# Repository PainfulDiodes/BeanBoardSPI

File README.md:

# BeanBoardSPI

_SPI controller in 74' logic for [BeanBoard](https://github.com/PainfulDiodes/BeanBoard) / [BeanZee](https://github.com/PainfulDiodes/BeanZee) Z80 computer._

SPI is a fast serial interface commonly used for connecting microcontrollers to peripherals like SD cards, displays and sensors.

The intent of this design is to provide access to an [RA8875](https://www.adafruit.com/product/1590) TFT panel controller and to [flash memory modules](https://www.adafruit.com/product/5635) on my Z80 homebrew computer. The [Marvin](https://github.com/PainfulDiodes/marvin) monitor program provides software support for this configuration.

For background, please see the [accompanying blog posts](https://painfuldiodes.wordpress.com/category/beanboardspi/).

*Thank you to those helpful folks at [PCBWay](https://pcbway.com) who sponsored this build and provided the PCBs*

&nbsp;

BeanBoardSPI Rev B populated with Adafruit SPI modules

SPI timing

BeanBoardSPI Rev A Plugged into BeanBoard with BeanZee, and a TFT panel

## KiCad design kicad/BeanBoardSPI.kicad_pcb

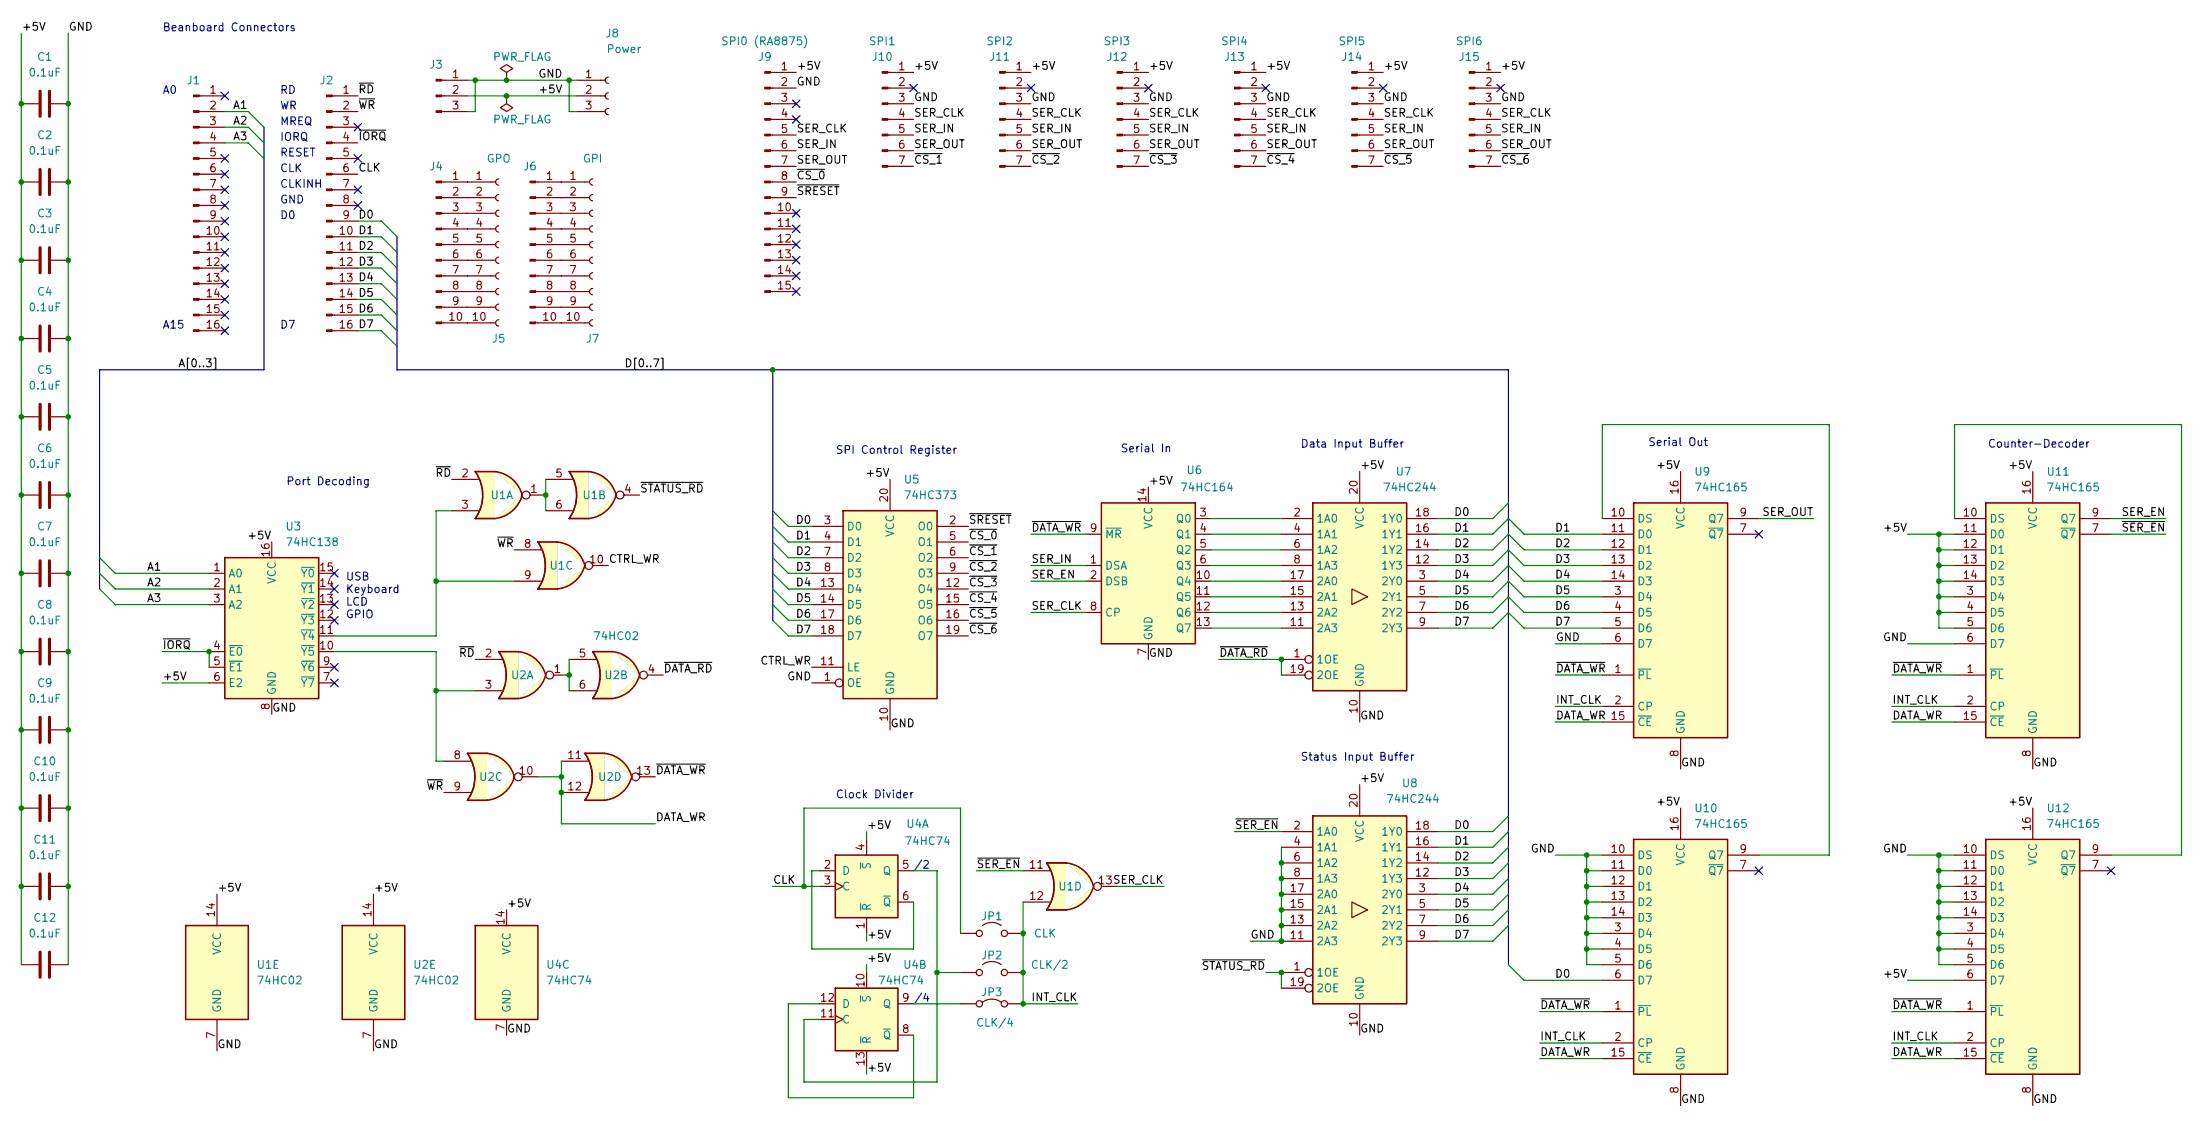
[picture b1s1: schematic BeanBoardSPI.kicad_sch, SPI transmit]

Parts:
C1, C2, C3, C4, C5, C6, C7, C8, C9, C10, C11, C12: 0.1uF; C_Disc_D5.0mm_W2.5mm_P2.50mm
J1, J2: Conn_01x16_Pin; PinHeader_1x16_P2.54mm_Vertical
J3: Conn_01x03_Pin; PinHeader_1x03_P2.54mm_Vertical
J4, J6: Conn_01x10_Pin; PinHeader_1x10_P2.54mm_Vertical
J5: GPO; PinSocket_1x10_P2.54mm_Vertical
J7: GPI; PinSocket_1x10_P2.54mm_Vertical
J8: Power; PinSocket_1x03_P2.54mm_Vertical
J9: SPI0 (RA8875); PinHeader_1x15_P2.54mm_Vertical
J10: SPI1; PinHeader_1x07_P2.54mm_Vertical
J11: SPI2; PinHeader_1x07_P2.54mm_Vertical
J12: SPI3; PinHeader_1x07_P2.54mm_Vertical
J13: SPI4; PinHeader_1x07_P2.54mm_Vertical
J14: SPI5; PinHeader_1x07_P2.54mm_Vertical
J15: SPI6; PinHeader_1x07_P2.54mm_Vertical
JP1: CLK; PinHeader_1x02_P2.54mm_Vertical
JP2: CLK/2; PinHeader_1x02_P2.54mm_Vertical
JP3: CLK/4; PinHeader_1x02_P2.54mm_Vertical
U1, U2: 74HC02; DIP-14_W7.62mm_Socket
U3: 74HC138; DIP-16_W7.62mm_Socket
U4: 74HC74; DIP-14_W7.62mm_Socket
U5: 74HC373; DIP-20_W7.62mm_Socket
U6: 74HC164; DIP-14_W7.62mm_Socket
U7, U8: 74HC244; DIP-20_W7.62mm_Socket
U9, U10, U11, U12: 74HC165; DIP-16_W7.62mm_Socket

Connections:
/+5V: C1.1, C2.1, C3.1, C4.1, C5.1, C6.1, C7.1, C8.1, C9.1, C10.1, C11.1, C12.1, J3.2, J8.2, J9.1, J10.1, J11.1, J12.1, J13.1, J14.1, J15.1, U1.14 (VCC), U2.14 (VCC), U3.6 (E2), U3.16 (VCC), U4.1 (~R), U4.4 (~S), U4.10 (~S), U4.13 (~R), U4.14 (VCC), U5.20 (VCC), U6.14 (VCC), U7.20 (VCC), U8.20 (VCC), U9.16 (VCC), U10.16 (VCC), U11.3 (D4), U11.4 (D5), U11.5 (D6), U11.11 (D0), U11.12 (D1), U11.13 (D2), U11.14 (D3), U11.16 (VCC), U12.6 (D7), U12.16 (VCC)
/A1: J1.2, U3.1 (A0)
/A2: J1.3, U3.2 (A1)
/A3: J1.4, U3.3 (A2)
/CLK: J2.6, JP1.1 (A), U4.3 (C)
/CTRL_WR: U1.10, U5.11 (LE)
/D0: J2.9, U5.3 (D0), U7.18 (1Y0), U8.18 (1Y0), U10.6 (D7)
/D1: J2.10, U5.4 (D1), U7.16 (1Y1), U8.16 (1Y1), U9.11 (D0)
/D2: J2.11, U5.7 (D2), U7.14 (1Y2), U8.14 (1Y2), U9.12 (D1)
/D3: J2.12, U5.8 (D3), U7.12 (1Y3), U8.12 (1Y3), U9.13 (D2)
/D4: J2.13, U5.13 (D4), U7.3 (2Y0), U8.3 (2Y0), U9.14 (D3)
/D5: J2.14, U5.14 (D5), U7.5 (2Y1), U8.5 (2Y1), U9.3 (D4)
/D6: J2.15, U5.17 (D6), U7.7 (2Y2), U8.7 (2Y2), U9.4 (D5)
/D7: J2.16, U5.18 (D7), U7.9 (2Y3), U8.9 (2Y3), U9.5 (D6)
/DATA_WR: U2.10, U2.11, U2.12, U9.15 (~CE), U10.15 (~CE), U11.15 (~CE), U12.15 (~CE)
/GND: C1.2, C2.2, C3.2, C4.2, C5.2, C6.2, C7.2, C8.2, C9.2, C10.2, C11.2, C12.2, J3.1, J3.3, J8.1, J8.3, J9.2, J10.3, J11.3, J12.3, J13.3, J14.3, J15.3, U1.7 (GND), U2.7 (GND), U3.8 (GND), U4.7 (GND), U5.1 (OE), U5.10 (GND), U6.7 (GND), U7.10 (GND), U8.4 (1A1), U8.6 (1A2), U8.8 (1A3), U8.10 (GND), U8.11 (2A3), U8.13 (2A2), U8.15 (2A1), U8.17 (2A0), U9.6 (D7), U9.8 (GND), U10.3 (D4), U10.4 (D5), U10.5 (D6), U10.8 (GND), U10.10 (DS), U10.11 (D0), U10.12 (D1), U10.13 (D2), U10.14 (D3), U11.6 (D7), U11.8 (GND), U12.3 (D4), U12.4 (D5), U12.5 (D6), U12.8 (GND), U12.10 (DS), U12.11 (D0), U12.12 (D1), U12.13 (D2), U12.14 (D3)
/INT_CLK: JP1.2 (B), JP2.2 (B), JP3.2 (B), U1.12, U9.2 (CP), U10.2 (CP), U11.2 (CP), U12.2 (CP)
/SER_CLK: J9.5, J10.4, J11.4, J12.4, J13.4, J14.4, J15.4, U1.13, U6.8 (CP)
/SER_EN: U6.2 (DSB), U11.9 (Q7)
/SER_IN: J9.6, J10.5, J11.5, J12.5, J13.5, J14.5, J15.5, U6.1 (DSA)
/SER_OUT: J9.7, J10.6, J11.6, J12.6, J13.6, J14.6, J15.6, U9.9 (Q7)
/~CS_0: J9.8, U5.5 (O1)
/~CS_1: J10.7, U5.6 (O2)
/~CS_2: J11.7, U5.9 (O3)
/~CS_3: J12.7, U5.12 (O4)
/~CS_4: J13.7, U5.15 (O5)
/~CS_5: J14.7, U5.16 (O6)
/~CS_6: J15.7, U5.19 (O7)
/~DATA_RD: U2.4, U7.1 (1OE), U7.19 (2OE)
/~DATA_WR: U2.13, U6.9 (~MR), U9.1 (~PL), U10.1 (~PL), U11.1 (~PL), U12.1 (~PL)
/~IORQ: J2.4, U3.4 (~E0), U3.5 (~E1)
/~RD: J2.1, U1.2, U2.2
/~SER_EN: U1.11, U8.2 (1A0), U11.7 (~Q7)
/~SRESET: J9.9, U5.2 (O0)
/~STATUS_RD: U1.4, U8.1 (1OE), U8.19 (2OE)
/~WR: J2.2, U1.8, U2.9
unnamed: J4.1, J5.1
unnamed: J4.2, J5.2
unnamed: J4.3, J5.3
unnamed: J4.4, J5.4
unnamed: J4.5, J5.5
unnamed: J4.6, J5.6
unnamed: J4.7, J5.7
unnamed: J4.8, J5.8
unnamed: J4.9, J5.9
unnamed: J4.10, J5.10
unnamed: J6.1, J7.1
unnamed: J6.2, J7.2
unnamed: J6.3, J7.3
unnamed: J6.4, J7.4
unnamed: J6.5, J7.5
unnamed: J6.6, J7.6
unnamed: J6.7, J7.7
unnamed: J6.8, J7.8
unnamed: J6.9, J7.9
unnamed: J6.10, J7.10
unnamed: JP2.1 (A), U4.5 (Q), U4.11 (C)
unnamed: JP3.1 (A), U4.9 (Q)
unnamed: U1.1, U1.5, U1.6
unnamed: U2.1, U2.5, U2.6
unnamed: U1.3, U1.9, U3.11 (~Y4)
unnamed: U2.3, U2.8, U3.10 (~Y5)
unnamed: U4.2 (D), U4.6 (~Q)
unnamed: U4.8 (~Q), U4.12 (D)
unnamed: U6.3 (Q0), U7.2 (1A0)
unnamed: U6.4 (Q1), U7.4 (1A1)
unnamed: U6.5 (Q2), U7.6 (1A2)
unnamed: U6.6 (Q3), U7.8 (1A3)
unnamed: U6.10 (Q4), U7.17 (2A0)
unnamed: U6.11 (Q5), U7.15 (2A1)
unnamed: U6.12 (Q6), U7.13 (2A2)
unnamed: U6.13 (Q7), U7.11 (2A3)
unnamed: U9.10 (DS), U10.9 (Q7)
unnamed: U11.10 (DS), U12.9 (Q7)

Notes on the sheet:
Status Input Buffer
A15
Port Decoding
USB Keyboard LCD GPIO
SPI Control Register
RESET
Serial In
MREQ
Counter-Decoder
Clock Divider
IORQ
Beanboard Connectors
CLKINH
Data Input Buffer
CLK
GND
Serial Out

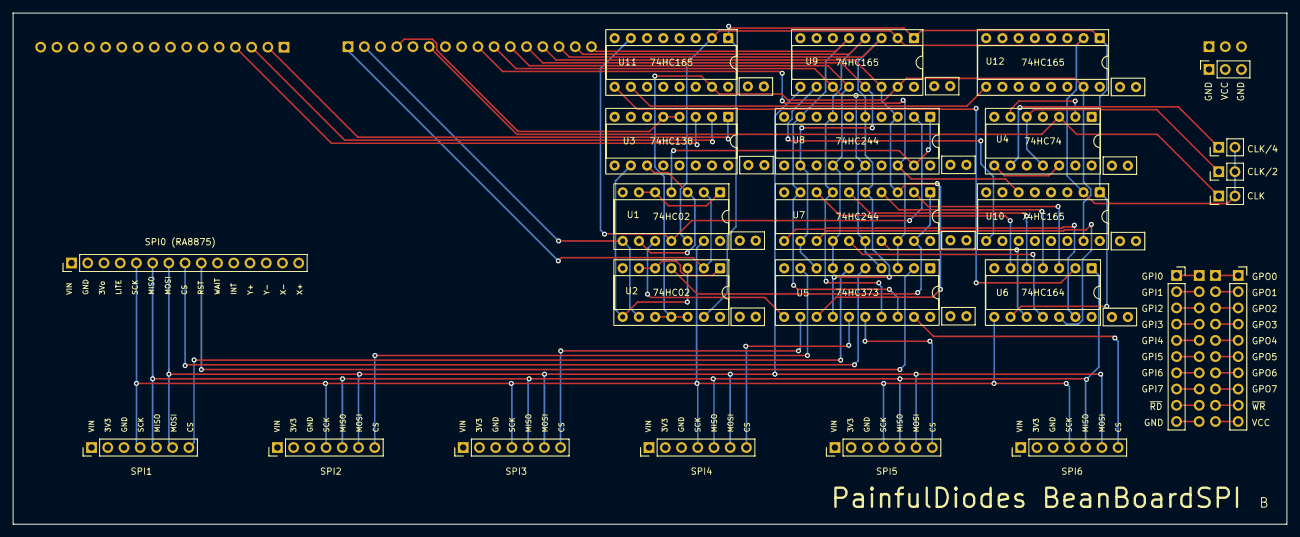
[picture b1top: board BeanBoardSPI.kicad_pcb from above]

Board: 4 copper layers, 199.4 x 80.0 mm, 42 parts (0 on the bottom side), 74 nets.

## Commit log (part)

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2026-01-19 initial commit
    copied from experiment, and minor changes
2026-01-31 Create fp-lib-table
2026-01-31 gerber
2026-02-23 alpha naming, photos
2026-02-27 additional Digital sims and updated readme
2026-04-24 Additional image of populated BeanBoardSPI
2026-05-27 sponsorship
2026-06-03 reset design for prototype 2
2026-06-04 Update BeanBoardSPI.dig
    Rewire internal CS logic
2026-06-04 Update BeanBoardSPI.dig
    added Z80 and SPI Control Register
2026-06-04 Update BeanBoardSPI.dig
    wired up the output register to the Z80 data bus
2026-06-05 Update BeanBoardSPI.dig
    change labels
2026-06-05 Update BeanBoardSPI.dig
    data read buffer
2026-06-05 Update BeanBoardSPI.dig
    port decoding
2026-06-05 Update BeanBoardSPI.dig
    clock divider
2026-06-05 Update BeanBoardSPI.dig
    tidy
2026-06-05 Update BeanBoardSPI.dig
    fix the z80 simulation of output date (correction to the timing)
2026-06-10 Upgraded KiCAD 10.0.1
2026-06-10 schematic
2026-06-11 align labels between simulation and schematic
2026-06-11 schemaric
2026-06-12 schematic files tidy
2026-06-18 Update BeanBoardSPI.kicad_sch
    added status input buffer and port decoding logic
2026-06-18 rationalised fro chip count
    replaced interters with NORs
2026-06-18 Update BeanBoardSPI.kicad_pcb
    mounting hole
2026-06-19 schematic
    tidy footprints symbols
2026-06-19 schematic
    remove unused libraries
2026-06-19 schematic
    update project libs
2026-06-20 schematic
    renumber components
2026-06-20 layout
    footprints
2026-06-20 schematic / layout
    tidy
2026-06-20 layout / schematic
    position components
2026-06-20 layout
    silk screen
2026-06-20 layout / schematic
    clock divider labelling
2026-06-21 Update BeanBoardSPI.kicad_pcb
    cap positioning
2026-06-21 Update BeanBoardSPI.kicad_pcb
    tracks - data
2026-06-21 Update BeanBoardSPI.kicad_pcb
    data / ser data tracks
2026-06-23 gerbers
